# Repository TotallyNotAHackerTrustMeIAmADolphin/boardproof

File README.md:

# boardproof

An MCP server for PCB design in which nothing counts as finished unless a machine-checked gate says so. The Python package is `boardproof` and the start command is `boardproof`.

An MCP server that lets an AI agent do PCB design work in KiCad: component sourcing, schematic construction, placement, routing (KiCadRoutingTools or Freerouting), verification, SPICE simulation and manufacturing export. It drives KiCad through its files and `kicad-cli`, so no running KiCad is needed.

Who it is for: people who want an MCP client (Claude Code, Claude Desktop or another) to carry out real KiCad 10 work and who care more about a result they can trust than about a result that looks finished. Everything is built around one rule: a board is "done" only when a machine-checked verdict says so. A short tour of the design is in [docs/OVERVIEW.md](docs/OVERVIEW.md).

## Status (2026-10-29)

**No board has passed the acceptance gate as a plain PASS yet.** The tools exist and are tested, but no tool chain has delivered a routed board end to end that the gate accepts without a qualifier. Rung 1 has boards with `PASS (necked)` (protocol 6, Freerouting 5 of 5); the rung-1 board changed afterwards (protocols 7 and 8) and has no official batch under the current protocol. The product promise is therefore tiered by board class:

- **Copilot tier (default):** you own power routing and zone topology in KiCad. The agent handles schematic, placement, signal routing and verification.
- **Autonomous tier:** offered only for board classes that have passed the gate on the acceptance ladder. **Currently none.**

Words used below: a **rung** is one reference board on the acceptance ladder (an ordered set of boards a pipeline must pass, easiest first); **KRT** is KiCadRoutingTools, a third-party router this project runs as a subprocess; the **owner** is the person who decides the scope and rules of this project; a **build ticket N** is an internal work item id and may not be resolvable in a public copy (the fact is always stated in words next to it); a **protocol** is the frozen, numbered plan by which a rung is measured. [docs/CONTEXT.md](docs/CONTEXT.md) has the full glossary.

What the measurements say (five attempts per backend and rung, official batches, 2026-10-28):

| Rung | Board | Protocol | Freerouting 2.5.0 | KiCadRoutingTools 0.23.1 |
|---|---|---|---|---|
| 1 | USB-C ATtiny1616 breakout, 2 layers | 6 | 5 of 5 attempts `PASS (necked)` | 0 of 5 |
| 2 | KiCad's `pic_programmer` demo, tracks removed | 5 (no protocol-6 batch has run) | 0 of 5; cannot pass | 0 of 5; cannot pass |

- **`PASS (necked)`** means the board passed the gate (zero unconnected items, zero error-level DRC violations, all zones filled), but it carries counted necks: tracks narrower than their net class right at a pad entry, which the protocol accepts as "forced" when the pad geometry limits the width (at the 0.2 mm gap between U1's pads, a 0.2 mm track is the widest that keeps the class clearance). The Freerouting boards carry 3 such necks on `+3V3` at U1 pad 4, 2.1476 mm in total. It is a weaker statement than a plain PASS, it is always labelled, and no rung is claimed from it.
- **The 5 of 5 depends on one open decision.** The first segment of each neck is 0.15 mm wide where the pad would allow 0.2 mm. Under the protocol's current reading that still counts as forced; under a stricter reading all five attempts would FAIL. The owner's decision on a neck below the pad limit is still open (build ticket 111, item 3).
- KiCadRoutingTools scored 0 of 5 on rung 1 under protocol 6 because version 0.23.1 read the board's 10 unquoted pad names of the USB-C footprint as zero pads. The board and the router checkout have since changed (the checkout is pinned to a newer commit) and no official batch has run on them yet (build ticket 112 holds the guard).
- Rung 2 cannot pass for any router: the demo's own silkscreen already carries 6 `silk_overlap` errors, which no router can fix (build ticket 106).
- Rung 3, the 20 A class openMPPT board, is frozen until rungs 1 and 2 pass.

Details and the exact meaning of each number: [docs/ROADMAP.md](docs/ROADMAP.md) and [docs/TESTING.md](docs/TESTING.md).

## Quickstart

1. Install (below) and add the server to your MCP client (below).
2. Ask the agent to open a project: `project_open` takes a project directory or a `.kicad_pro` file. `project_create` scaffolds a new one.
3. Load what you need: `list_toolsets` shows the toolsets, `load_toolset` loads one (`schematic`, `placement`, `routing`, ...).
4. Grade the board: `pin_rule_baseline` before you start work, then `verify_board` with the board path, `parity="required"` (or `"not_applicable"` with a reason) and the baseline. Only a `PASS` from `verify_board` may be called routed or done.

## Install

Requirements:

- Python 3.11 or newer.
- KiCad 10 with `kicad-cli` (required). Tested with 10.0.7.
- Tested on Windows only (Windows 11, KiCad 10.0.7): every measurement and every gate run was made there. The code does not knowingly depend on Windows, but nothing has been run on Linux or macOS. Where docs/TESTING.md names Ubuntu paths, they are KiCad's package layout, not something this project has run.

Clone with submodules, so the JLCPCB library comes along (about 103 MB; it is optional, see below):

```
git clone --recurse-submodules <repository-url>
cd <the cloned folder>
```

Already cloned without them? `git submodule update --init --depth 1` fetches them afterwards.

```
python -m venv .venv
.venv/Scripts/pip install -e ".[dev,krt]"
```

easyeda2kicad (AGPL-3.0) is a core dependency, installed with the package and used as a subprocess only, never imported. Extras: `dev` (pytest, ruff), `krt` (the runtime dependencies of KiCadRoutingTools: numpy, scipy, shapely, Pillow), `copilot` (kicad-python, for the live-IPC adapter).

### External tools

Each tool is found the same way: an environment variable first, then `PATH`, then the usual install locations. A missing tool makes the tools that need it return `status: incomplete` with install instructions, never a guess.

| Tool | Used for | Environment variable |
|---|---|---|
| KiCad 10 `kicad-cli` | **Required.** DRC, ERC, netlists, renders, exports, the gate | `KICAD_CLI_PATH` |
| KiCad's bundled Python | Freerouting's Specctra export and import; KiKit | `KICAD_PYTHON_PATH` |
| KiCadRoutingTools v0.23.8, commit `c64c0db2` (MIT) | Routing and placement optimisation, run from a checkout. `python scripts/setup_krt.py` restores it into `.tools/KiCadRoutingTools` (the default; the variable wins) and fetches its prebuilt router, verified by SHA-256 | `KICAD_ROUTING_TOOLS_PATH`, `KICAD_ROUTING_TOOLS_PYTHON` |
| Freerouting 2.5.0 jar (GPLv3) and Java 25 | Routing, as a subprocess | `FREEROUTING_JAR_PATH`, `JAVA_PATH` |
| ngspice 47 (pinned; `ngspice_con.exe` on Windows) | SPICE simulation. **Optional while the simulation map is parked** (owner decision of 2026-10-30, issue 40): the batch gate does not require it, and its live tests skip, counted, when it is absent | `NGSPICE_PATH` |
| KiKit | Panelisation | `KIKIT_PATH` |
| KiCad's demo projects | Inputs of the second rung and of the oracle tests | `KICAD_DEMOS_DIR` |
| KiCad's symbol libraries | Schematic building and tests | `KICAD_SYMBOL_DIR` |

All third-party tools, their licences and how they are used are listed in [THIRD_PARTY.md](THIRD_PARTY.md).

### Optional: the JLCPCB symbol and footprint library

Whether a part is a JLCPCB Basic, Preferred or Extended part is answered from a small index that ships with the repository, with no download. The ready-made symbols, footprints and 3D models behind that index (CDFER/JLCPCB-Kicad-Library, MIT, about 103 MB) are a git submodule that a plain `git clone` does not fetch. Fetch it when you want them:

```
git submodule update --init --depth 1 third_party/JLCPCB-Kicad-Library
```

Without it, asset lookups fall back to `easyeda2kicad` (a core dependency) and say so. The server looks for the library in this order: the `BOARDPROOF_JLCPCB_LIBRARY` environment variable, the submodule above, KiCad's third-party directory (a Plugin and Content Manager install). `jlcpcb_library_status` reports what it found and, for an empty or missing submodule, the command above. A new git worktree starts with the submodule empty; set `BOARDPROOF_JLCPCB_LIBRARY` to another checkout's `third_party/JLCPCB-Kicad-Library` to share it. To rebuild the index after moving the pin: `python scripts/refresh_jlcpcb_index.py`.

#### Refreshing the library to upstream's newest commit

The pin stays on one commit so the shipped index is reproducible. To move it, run in a checkout whose submodule is initialised (the command above), from a clean tree:

```
python scripts/refresh_jlcpcb_index.py --update --dry-run   # plan only: fetches into a scratch repository, changes nothing here
python scripts/refresh_jlcpcb_index.py --update             # moves the pin, rewrites the index, stages both
```

It prints upstream's commit, the part counts and every part that changes tier (Basic, Preferred, Extended), then stages the new submodule commit and the index; you review and commit. It refuses, and moves nothing, when a symbol library that holds parts today holds none upstream (`library_emptied`), when the part count falls below 80% of the old one (`index_would_shrink`) or when a symbol file fails to parse. There is no override flag: to follow a real loss, move the pin by hand. The apply is all-or-nothing: if the index replace, the submodule checkout or `git add` fails, the old submodule commit, the old index bytes and the old staging are put back (or the exact commands to do so are printed). `--ref` must be a plain ref name and `--upstream` an https URL (a local directory only when typed on the command line); every fetch runs with `--` and with all git transports except https (and a typed local path) switched off. Upstream's newest commit was still broken when this was written (18 of 20 symbol files hold only a header), so the command refuses it today. Without the submodule the dry run works and the real run says what to fetch first.

## MCP client configuration

```json
{
  "mcpServers": {
    "boardproof": {
      "command": "path/to/.venv/Scripts/python",
      "args": ["-m", "boardproof.server"]
    }
  }
}
```

The installed script does the same: `"command": "path/to/.venv/Scripts/boardproof"` with no arguments.

Renamed from kicad-mcp (package `kicad_mcp`, environment prefix `KICAD_MCP_`) in build ticket 74: the package, the start command and the MCP server name are `boardproof`, and the environment variables `KICAD_MCP_*` are now `BOARDPROOF_*` with no fallback. After pulling the rename run `pip install -e .` again in the virtual environment and change the MCP client configuration (`-m kicad_mcp.server` becomes `-m boardproof.server`). Schematic backups made before the rename stay in the old backup directory (`%LOCALAPPDATA%\kicad-mcp\schematic-backups`) and are not read by the new name.

The server starts with 19 tools: the three toolset tools (`list_toolsets`, `load_toolset`, `unload_toolset`), `project_create`, `project_open`, the gate (`verify_board`, `pin_rule_baseline`) and the checkpointed pairs for input preparation, pour step, schematic import, board rules, board outline and silkscreen minimums. Ten more toolsets load on demand with `load_toolset`: `verification` (9 tools), `sourcing` (13), `diagnostics` (2), `library` (3), `schematic` (7), `placement` (12), `manufacturing` (2), `routing` (6), `copilot` (9) and `simulation` (2). That is 65 more tools, 84 in total (counted from a running server on 2026-10-29).

## Usage log (local, anonymous, off with one variable)

The server keeps a small log of which of its own tools get called, so that unused tools can be found and slow ones fixed. It is **on by default and stays on your machine**: nothing is sent anywhere, and the logging code imports no networking module (a test checks it).

- **What is recorded**, one JSON line per tool call: the UTC start time, the tool's name, its toolset, the duration in milliseconds, the outcome (one of a fixed set of words: `ok`, `error`, `cancelled`, or the result's own status word such as `PASS`, `FAIL` or `INCOMPLETE` if it is on the reviewed list in `usage_log.RESULT_WORDS`; any other word is recorded as `other`, never copied) and a random id that is new for each server process.
- **What is never recorded:** arguments, results, file paths, part numbers, net names, user or machine names, environment values.
- **Where:** `usage.jsonl` in the `boardproof` folder of `%LOCALAPPDATA%` on Windows, `~/Library/Application Support/boardproof/usage.jsonl` on macOS, `$XDG_DATA_HOME/boardproof/usage.jsonl` (else `~/.local/share/boardproof/usage.jsonl`) elsewhere. The file is capped at 1 MB and rotates once to `usage.jsonl.1`. Set `BOARDPROOF_USAGE_LOG` to a file path to write there instead.
- **Turn it off:** set `BOARDPROOF_USAGE_LOG=off` in the server's environment (for example in the `env` block of the MCP client configuration). **Delete it:** delete `usage.jsonl` and `usage.jsonl.1`.
- **Read it:** `python scripts/usage_report.py` prints, per tool, the count, share, median and 95th-percentile duration, error rate and last use, then the tools that were never called (`--since DAYS`, `--json`, `--log FILE`).

## Principles

- **Evidence-gated:** a check that did not fully run says so and never reports clean.
- **`kicad-cli` is the judge:** structured DRC and ERC output, read in full. Renders are for humans only.
- **Batch tools:** operations take collections, not one item per call.
- **Checkpoints:** autorouting, autoplacement, ambiguous part matches and destructive edits return a proposal and a revision token. Nothing is written until you confirm, and for the newer checkpoint pairs a confirm is refused if the project's files changed in between.
- **Never hand-edit KiCad files:** every mutation goes through this project's tools, or through the project's write layer (`boardproof.write_layer`), which saves through a temporary file, a parse check and `os.replace`.

## Limitations

- **Sourcing:** Nexar and Digi-Key providers are not built (they need credentials). The LCSC provider is blocked by a bot wall and returns an error rather than an empty list. The JLCPCB Basic parts index is vendored.
- **Autoplacement** (`propose_autoplacement`) is a naive row-packer. KiCadRoutingTools' placement optimiser is the stronger option.
- **Zones:** there is a pour step (`propose_pour_step` and `confirm_pour_step`) that adds a gate-graded plane zone from KiCadRoutingTools' plane script. There is no general zone-editing tool and no track or via removal tool.
- **Schematic editing tools** are unsafe on hierarchical (multi-sheet) projects; see [docs/ARCHITECTURE.md](docs/ARCHITECTURE.md), "Known facts and gotchas".
- **Windows only** so far.

## Tests

Several thousand tests (the current count is the last line of `python -m pytest --collect-only -q -m "not network"`). From the repository root:

```
python -m pytest -m "not network"
```

Tests that need an external tool skip with a stated reason when the tool is absent. The full gate, `python scripts/batch_gate.py`, runs the whole suite and the linter in a clean tree and ends with one `GREEN` or `RED` line; it takes about 45 minutes. There is no hosted CI: that local gate is the test gate. See [docs/TESTING.md](docs/TESTING.md).

## Documentation

| File | Contents |
|---|---|
| [docs/OVERVIEW.md](docs/OVERVIEW.md) | A ten-minute tour: how a tool call works, the gate, the ladder |
| [docs/CONTEXT.md](docs/CONTEXT.md) | Glossary |
| [docs/ARCHITECTURE.md](docs/ARCHITECTURE.md) | The decision record and the known facts and gotchas, with evidence |
| [docs/ROADMAP.md](docs/ROADMAP.md) | The acceptance ladder, carried-over defects, non-goals |
| [docs/TESTING.md](docs/TESTING.md) | The acceptance gate and the test suite |
| [CONTRIBUTING.md](CONTRIBUTING.md) | How to contribute |
| [THIRD_PARTY.md](THIRD_PARTY.md) | Third-party tools and data, with licences |
| [CLAUDE.md](CLAUDE.md) | Rules for AI agents working in this repository |

## Contributing and licence

Contributions are welcome; read [CONTRIBUTING.md](CONTRIBUTING.md) first. The code is MIT-licensed ([LICENSE](LICENSE)). Copyleft tools (Freerouting, easyeda2kicad) are only ever run as subprocesses. `kiutils` (GPLv3) is not used.

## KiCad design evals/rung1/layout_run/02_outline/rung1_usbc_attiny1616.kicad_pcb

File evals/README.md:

# Evaluation suite

`boardproof_eval.xml` holds 15 independent, read-only Q&A pairs. Each tests whether an agent with only this project's tools can answer a realistic question about the fixtures in `tests/fixtures/`. The format follows the `mcp-builder` evaluation guide. The suite tests tool usability, not board quality; the acceptance gate (docs/TESTING.md) handles that.

- **Q1-Q10:** single-tool lookups (DRC/ERC on `simple_led`, footprint counts, symbol values, the parametric footprint generator, datasheet extraction).
- **Q11-Q15:** multi-step chains:
  - Q11: collision check, then placement check.
  - Q12: DRC, then the unrouted-net query ("0 violations" does not mean fab-ready).
  - Q13: ERC, then SPICE export, then reading the netlist.
  - Q14: datasheet, then footprint generation, then minimal KLC.
  - Q15: open the project, run the manufacturing export, read the BOM and CPL.

## Rules for answers

- Every answer must be derived by **running the tool against the real fixture**, never by reasoning it out.
- **Pin answers to facts the fixture file determines,** not to facts the toolchain determines. `lib_footprint_mismatch` counts follow whichever KiCad stock libraries are installed, and they have already drifted once (1 became 3). Values set by `kicad_tools` internals are stated as properties ("at least 7 package types") and not as exact values.
- **No question depends on a live sourcing provider.**
- **No question mutates a fixture.** Exports go to temporary directories.

## Running

Use the `mcp-builder` evaluation script (`~/.claude/skills/mcp-builder/scripts/evaluation.py`) against this server. Or run it by hand: give an agent the tools and the questions, then diff its answers against the `<answer>` values.

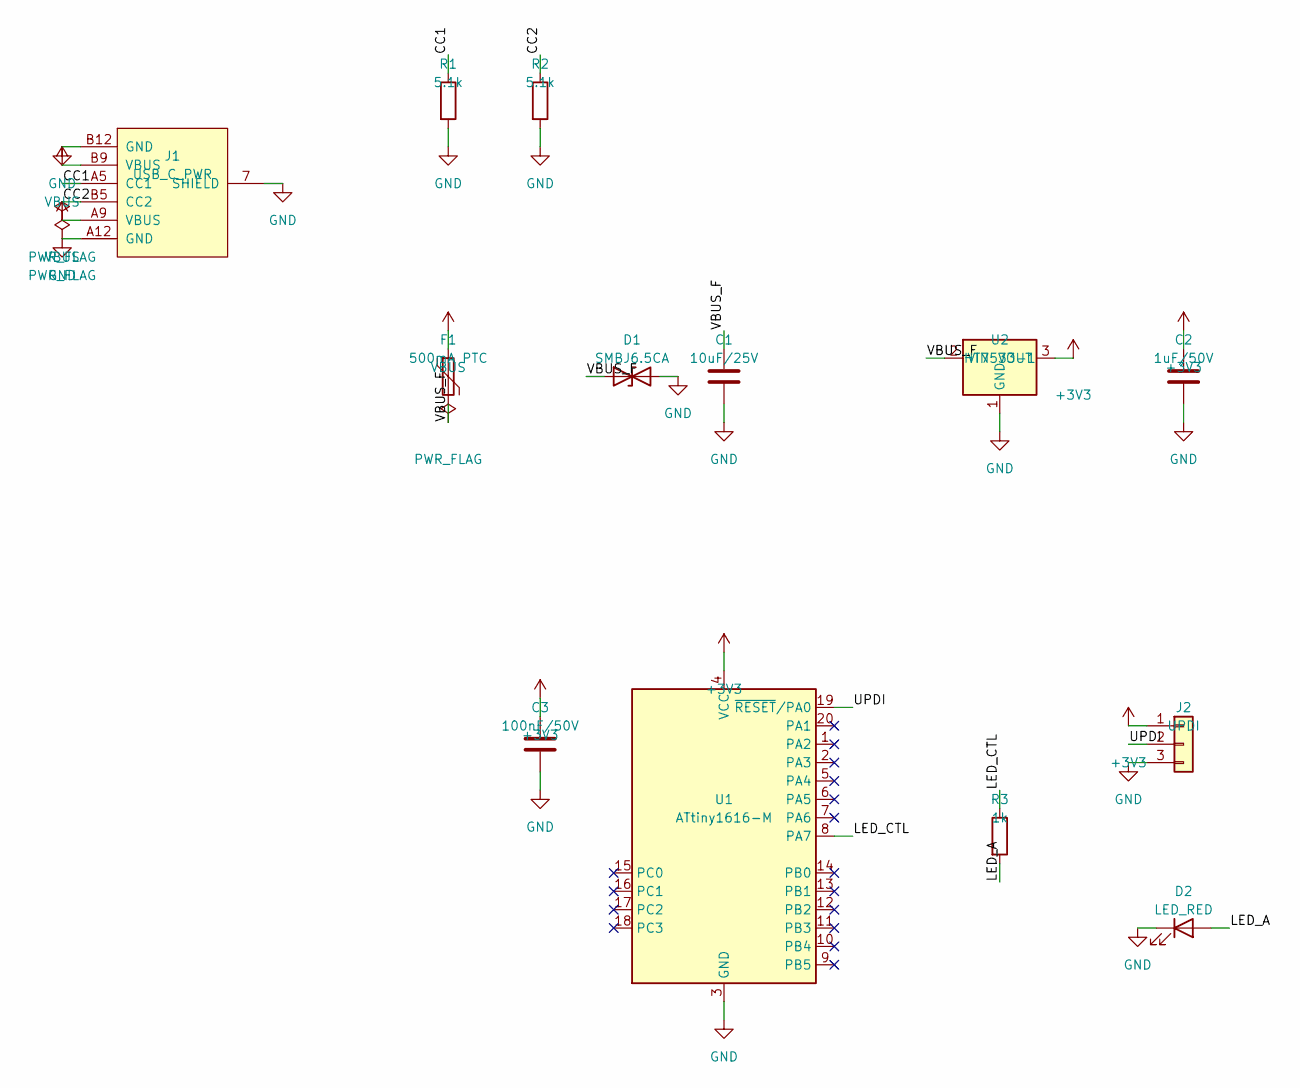
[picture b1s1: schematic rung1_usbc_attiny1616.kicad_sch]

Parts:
C1: 10uF/25V; C_0805_2012Metric; MPN CL21A106KAYNNNE; LCSC C15850
C2: 1uF/50V; C_0603_1608Metric; MPN CL10A105KB8NNNC; LCSC C15849
C3: 100nF/50V; C_0603_1608Metric; MPN CC0603KRX7R9BB104; LCSC C14663
D1: SMBJ6.5CA; D_SMB; MPN SMBJ6.5CA; LCSC C7420377
D2: LED_RED; LED_0603_1608Metric; MPN KT-0603R; LCSC C2286
F1: 500mA PTC; Fuse_0805_2012Metric; MPN SMD0805P050TF; LCSC C20978
J1: USB_C_PWR; USB_C_Receptacle_Shouhan_TYPE-C-6P; MPN TYPE-C 6P (SHOU HAN); LCSC C456012
J2: UPDI; PinHeader_1x03_P2.54mm_Vertical; MPN 2.54-1*3PIN (BOOMELE); LCSC C49257
R1, R2: 5.1k; R_0603_1608Metric; MPN 0603WAF5101T5E; LCSC C23186
R3: 1k; R_0603_1608Metric; MPN 0603WAF1001T5E; LCSC C21190
U1: ATtiny1616-M; VQFN-20-1EP_3x3mm_P0.4mm_EP1.7x1.7mm; MPN ATTINY1616-MNR; LCSC C507118
U2: HT7533-1; SOT-89-3; MPN HT7533-1; LCSC C14289

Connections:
+3V3: C2.1, C3.1, J2.1, U1.4 (VCC), U2.3 (VOUT)
/CC1: J1.A5 (CC1), R1.1
/CC2: J1.B5 (CC2), R2.1
/LED_A: D2.2 (A), R3.2
/LED_CTL: R3.1, U1.8 (PA7)
/UPDI: J2.2, U1.19 (~RESET/PA0)
/VBUS_F: C1.1, D1.1 (A1), F1.2, U2.2 (VIN)
GND: C1.2, C2.2, C3.2, D1.2 (A2), D2.1 (K), J1.7 (SHIELD), J1.A12 (GND), J1.B12 (GND), J2.3, R1.2, R2.2, U1.3 (GND), U1.21 (GND), U2.1 (GND)
VBUS: F1.1, J1.A9 (VBUS), J1.B9 (VBUS)

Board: 2 copper layers, 17 parts (0 on the bottom side), 9 nets, no tracks yet.

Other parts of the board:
H1, H2, H3, H4: MountingHole_2.2mm_M2

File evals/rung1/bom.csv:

Designator,Comment,Footprint,LCSC Part #,MPN,Tier
C1,10uF/25V,Capacitor_SMD:C_0805_2012Metric,C15850,CL21A106KAYNNNE,basic
C2,1uF/50V,Capacitor_SMD:C_0603_1608Metric,C15849,CL10A105KB8NNNC,basic
C3,100nF/50V,Capacitor_SMD:C_0603_1608Metric,C14663,CC0603KRX7R9BB104,basic
D1,SMBJ6.5CA,Diode_SMD:D_SMB,C7420377,SMBJ6.5CA,basic
D2,LED_RED,LED_SMD:LED_0603_1608Metric,C2286,KT-0603R,basic
F1,500mA PTC,Fuse:Fuse_0805_2012Metric,C20978,SMD0805P050TF,extended
J1,USB_C_PWR,Rung1_USBC:USB_C_Receptacle_Shouhan_TYPE-C-6P,C456012,TYPE-C 6P (SHOU HAN),extended
J2,UPDI,Connector_PinHeader_2.54mm:PinHeader_1x03_P2.54mm_Vertical,C49257,2.54-1*3PIN (BOOMELE),extended
R1,5.1k,Resistor_SMD:R_0603_1608Metric,C23186,0603WAF5101T5E,basic
R2,5.1k,Resistor_SMD:R_0603_1608Metric,C23186,0603WAF5101T5E,basic
R3,1k,Resistor_SMD:R_0603_1608Metric,C21190,0603WAF1001T5E,basic
U1,ATtiny1616-M,Package_DFN_QFN:VQFN-20-1EP_3x3mm_P0.4mm_EP1.7x1.7mm,C507118,ATTINY1616-MNR,extended
U2,HT7533-1,Package_TO_SOT_SMD:SOT-89-3,C14289,HT7533-1,basic

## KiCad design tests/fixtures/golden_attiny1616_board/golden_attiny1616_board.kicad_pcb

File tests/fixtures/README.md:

# Test fixtures

Every purpose-built fixture is generated through `kicad_tools`' own object model (`PCB.create`, footprints, nets, `SExp`) and saved through the write layer (`write_layer.save_pcb`, which parse-checks it with `kicad-cli`; build ticket 42), or filled by `kicad-cli`. None is hand-typed (CLAUDE.md rule 1).

| Fixture | Origin | Purpose |
|---|---|---|
| `simple_led.*` | Copied from rjwalters/kicad-tools `00-simple-led` (MIT) | Small, valid real KiCad files for `kicad-cli` and `kicad_tools` calls. KiCad 7-style refs, which is why it missed the KiCad 8+ DSN reference bug. |
| `golden_attiny1616_board/` | Built by the pipeline (v1, 2026-09-02) | Pipeline regression fixture. **Unrouted. It has a generic power header instead of USB-C, and its 0.2/0.2 rules cannot be routed at the VQFN's 0.4 mm pitch.** Not a rung-1 candidate (TESTING.md). |
| `graphics_removal_board.kicad_pcb` | Purpose-built | `propose_remove_graphic_items` tests: six graphics across `gr_rect`, `gr_poly`, `gr_line`, `gr_circle` and `gr_arc`, net-tagged copper plus silkscreen. |
| `zone_obstacle/` | `simple_led` plus a real GND pour filled by `kicad-cli --refill-zones` | Reproduces "filled zone is not an obstacle for a foreign net": KRT routes LED_ANODE at 0.0 mm clearance to the GND zone. |
| `krt_stress_congestion.*` | Purpose-built, 30x36 mm, 2-layer, with a real sibling `.kicad_pro` | KRT placement and blocking-analysis tests. An LQFP-48 with 5 signal nets crosses an 8-pin THT header wall, modelled on openMPPT's GPIO1 bottleneck. KRT routes 4 of 5 nets in about 4 s. `SIG5` fails as `boxed_in_static`, but `check_reachability.py` says the net is PASSABLE, so this is a search miss, not real congestion. |
| `krt_pad_geometry_isolated.*` | Purpose-built | Isolates whether pad size alone blocks a route. With 2.2 mm header pads (0.34 mm gap), `SIG1` fails after more than 227k A\* iterations. Shrunk to the JLCPCB floor of 1.36 mm (1.0 drill + 2 x 0.18 annular), it routes as one direct trace. The shrink must mutate the `(size)` node, because `pad.size = ...` is not saved. |
| `openmppt_v1_3.kicad_dru` | Copied from the user's openMPPT board | A real custom-rules file for `board_rules` matching (`hole_to_hole` vs `hole_clearance`). |
| `datasheets/` | TI LM358, onsemi NCV7691, Nexperia PMEG2005EJ | `inspect_datasheet` tests. |
| `uw/r2krt`, `uw/r1krt`, `uw/r1fr` | Taken byte-for-byte from the committed run directories of `paradigm-review-2` ticket 04 (2026-10-19, KRT rung 2, KRT rung 1, Freerouting rung 1): `in/` holds the batch's frozen `.kicad_pcb` and `.kicad_pro`, `out/` the board attempt 00 delivered; `attempt0.json` holds that attempt's recorded router facts with machine paths replaced by `<path>` (by `scripts/export_ladder_results.py`' sanitiser) | `tests/test_krt_under_width_delivery.py`, `tests/test_rung_backends_under_width.py`: the under-width replays. These were read from `.scratch` before the run directories left the repository. |

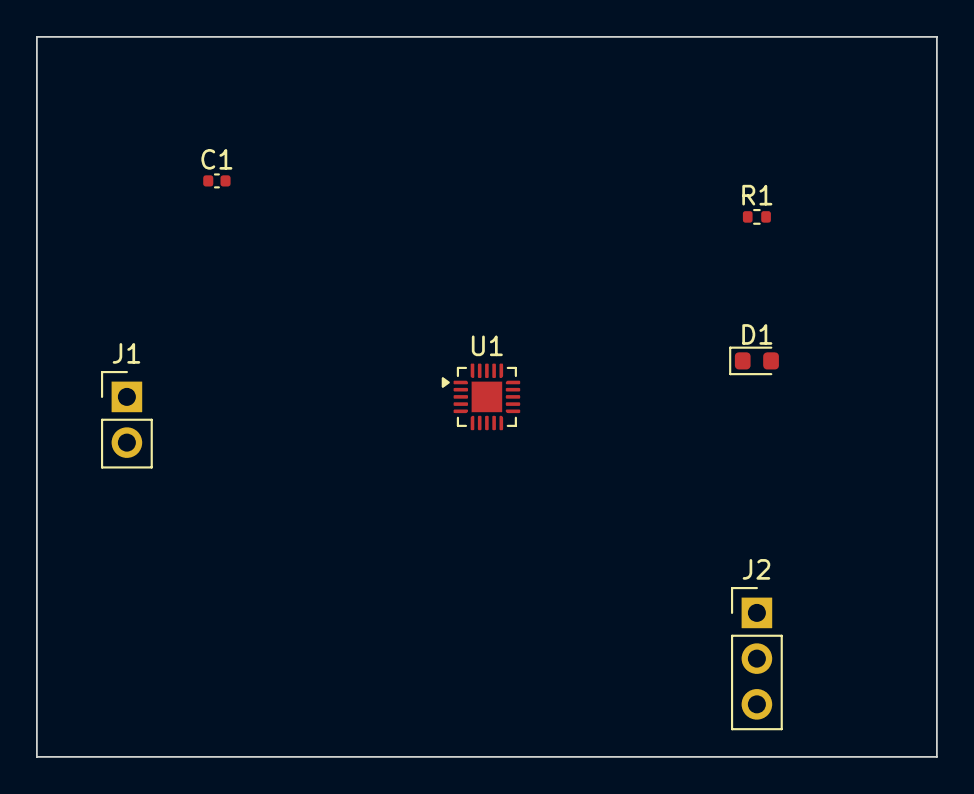
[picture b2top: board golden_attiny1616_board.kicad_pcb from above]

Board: 2 copper layers, 50.0 x 40.0 mm, 6 parts (0 on the bottom side), 5 nets, no tracks yet.

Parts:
C1: 100nF; C_0402_1005Metric
D1: LED; LED_0603_1608Metric
J1: PWR_IN; PinHeader_1x02_P2.54mm_Vertical
J2: UPDI; PinHeader_1x03_P2.54mm_Vertical
R1: 1k; R_0402_1005Metric
U1: ATtiny1616-M; VQFN-20-1EP_3x3mm_P0.4mm_EP1.7x1.7mm

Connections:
GND: C1.2, D1.2, J1.2, J2.3, U1.3, U1.21
unnamed: D1.1, R1.2
unnamed: J2.2, U1.19
unnamed: R1.1, U1.20
VCC: C1.1, J1.1, J2.1, U1.4

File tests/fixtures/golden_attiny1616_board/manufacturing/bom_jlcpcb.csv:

Comment,Designator,Footprint,LCSC Part #
100nF,C1,Capacitor_SMD:C_0402_1005Metric,
1k,R1,Resistor_SMD:R_0402_1005Metric,
ATtiny1616-M,U1,Package_DFN_QFN:VQFN-20-1EP_3x3mm_P0.4mm_EP1.7x1.7mm,
LED,D1,LED_SMD:LED_0603_1608Metric,
PWR_IN,J1,Connector_PinHeader_2.54mm:PinHeader_1x02_P2.54mm_Vertical,
UPDI,J2,Connector_PinHeader_2.54mm:PinHeader_1x03_P2.54mm_Vertical,

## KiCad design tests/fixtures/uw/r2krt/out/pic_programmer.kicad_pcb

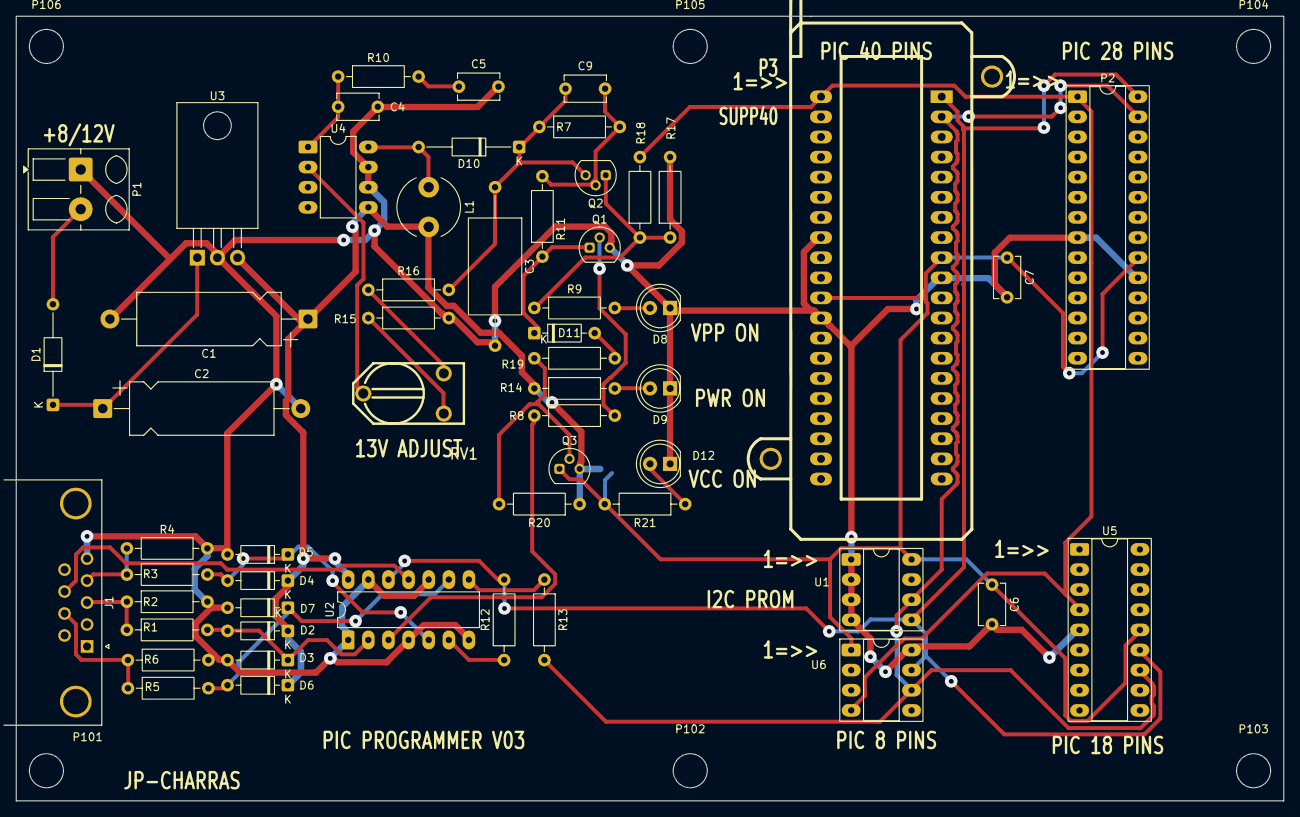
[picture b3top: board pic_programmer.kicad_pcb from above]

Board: 2 copper layers, 160.0 x 99.1 mm, 63 parts (1 on the bottom side), 34 nets.

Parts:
C1: 100µF; CP_Axial_L18.0mm_D6.5mm_P25.00mm_Horizontal
C2: 220uF; CP_Axial_L18.0mm_D6.5mm_P25.00mm_Horizontal
C3: 22uF/25V; C_Axial_L12.0mm_D6.5mm_P20.00mm_Horizontal
C4: 0; C_Disc_D5.1mm_W3.2mm_P5.00mm
C5: 10nF; C_Disc_D5.1mm_W3.2mm_P5.00mm
C6, C7: 100nF; C_Disc_D5.1mm_W3.2mm_P5.00mm
C9: 220nF; C_Disc_D5.1mm_W3.2mm_P5.00mm
D1: 1N4004; D_DO-35_SOD27_P12.70mm_Horizontal
D2, D3, D4, D5, D6, D7, D11: BAT43; D_DO-35_SOD27_P7.62mm_Horizontal
D8: RED-LED; LED_D5.0mm
D9: GREEN-LED; LED_D5.0mm
D10: SCHOTTKY; D_DO-35_SOD27_P12.70mm_Horizontal
D12: YELLOW-LED; LED_D5.0mm
J1: DB9-FEMAL; DSUB-9_Socket_Horizontal_P2.77x2.84mm_EdgePinOffset7.70mm_H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
JP1: JUMPER; SolderJumper-2_P1.3mm_Open_TrianglePad1.0x1.5mm
L1: 22uH; L_Radial_D7.8mm_P5.00mm_Fastron_07HCP
P1: CONN_2; Altech_AK300_1x02_P5.00mm_45-Degree
P2: SUPP28; DIP-28_W7.62mm_Socket_LongPads
P3: SUPP40; 40tex-Ell600
P101, P102, P103, P104, P105, P106: CONN_1; MountingHole_4.3mm_M4
Q1: BC237; TO-92
Q2, Q3: BC307; TO-92
R1, R2, R3, R4, R5, R6, R7: 10K; R_Axial_DIN0207_L6.3mm_D2.5mm_P10.16mm_Horizontal
R8: 1K; R_Axial_DIN0207_L6.3mm_D2.5mm_P10.16mm_Horizontal
R9, R19, R20: 2.2K; R_Axial_DIN0207_L6.3mm_D2.5mm_P10.16mm_Horizontal
R10: 5,1K; R_Axial_DIN0207_L6.3mm_D2.5mm_P10.16mm_Horizontal
R11, R17: 22K; R_Axial_DIN0207_L6.3mm_D2.5mm_P10.16mm_Horizontal
R12, R13, R14, R21: 470; R_Axial_DIN0207_L6.3mm_D2.5mm_P10.16mm_Horizontal
R15: 6.2K; R_Axial_DIN0207_L6.3mm_D2.5mm_P10.16mm_Horizontal
R16: 62K; R_Axial_DIN0207_L6.3mm_D2.5mm_P10.16mm_Horizontal
R18: 220; R_Axial_DIN0207_L6.3mm_D2.5mm_P10.16mm_Horizontal
RV1: 1K; RV2X4
U1: 24Cxx; DIP-8_W7.62mm_Socket_LongPads
U2: 74HC125; DIP-14_W7.62mm_LongPads
U3: 7805; TO-220-3_Horizontal_TabDown
U4: LT1373; DIP-8_W7.62mm_LongPads
U5: PIC_18_PINS; DIP-18_W7.62mm_Socket_LongPads
U6: PIC_8_PINS; DIP-8_W7.62mm_Socket_LongPads

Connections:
/CLOCK-RB6: P2.27, P3.39, R13.2, U1.6 (SCL), U5.12 (ICSPC/RB6), U6.6 (GP1)
/DATA-RB7: P2.28, P3.40, R12.2, U1.5 (SDA), U2.12, U5.13 (ICSPD/RB7), U6.7 (GP0)
/PC-CLOCK-OUT: J1.7, R5.1, R6.1
/PC-DATA-IN: J1.8, U2.11
/PC-DATA-OUT: J1.4, R3.1, R4.1
/VPP_ON: J1.3, R1.1, R2.1
/VPP/MCLR: P2.1, P3.1, R18.2, U5.4 (MCLR), U6.4 (GP3/MCLR)
/pic_sockets/VCC_PIC: C6.1, C7.1, JP1.2, P2.20, P3.11, P3.32, Q3.1 (C), R21.2, U1.8 (VCC), U5.14 (VDD), U6.1 (VDD)
GND: C1.2, C2.2, C3.2, C4.2, C5.2, C6.2, C7.2, D3.2 (A), D5.2 (A), D7.2 (A), D8.1 (K), D9.1 (K), D12.1 (K), J1.5, P1.1, P2.8, P2.19, P3.8, P3.12, P3.31, Q1.3 (E), R2.2, R4.2, R6.2, R15.2, R17.2, U1.1 (A0), U1.2 (A1), U1.3 (A2), U1.4 (GND), U2.1, U2.4, U2.7 (GND), U2.10, U2.13, U3.2 (GND), U4.6 (GND_S), U4.7 (GND), U5.5 (VSS), U6.8 (VSS)
unnamed: C5.1, R10.2
unnamed: D1.2 (A), P1.2 (PM)
unnamed: C2.1, D1.1 (K), U3.1 (VI)
unnamed: D2.2 (A), D3.1 (K), R1.2, U2.2
unnamed: D4.2 (A), D5.1 (K), R3.2, U2.5
unnamed: D6.2 (A), D7.1 (K), R5.2, U2.9
unnamed: D8.2 (A), R9.2
unnamed: D9.2 (A), R14.2
unnamed: D10.2 (A), L1.1, U4.8 (Vsw)
unnamed: D11.2 (A), R19.1
unnamed: D11.1 (K), Q1.1 (C), R11.1
unnamed: D12.2 (A), R21.1
unnamed: Q1.2 (B), R8.2
unnamed: C9.2, Q2.2 (B), R7.2, R11.2
unnamed: Q2.1 (C), R9.1, R17.1, R18.1
unnamed: Q3.2 (B), R19.2, R20.2
unnamed: R8.1, U2.3
unnamed: R12.1, U2.6
unnamed: R13.1, U2.8
unnamed: R15.1, RV1.1
unnamed: R16.1, RV1.3
unnamed: RV1.2, U4.2 (FB+)
unnamed: C4.1, R10.1, U4.1 (Vc)
VCC: C1.1, D2.1 (K), D4.1 (K), D6.1 (K), JP1.1, L1.2, Q3.3 (E), R14.1, R20.1, U2.14 (VCC), U3.3 (VO), U4.5 (Vin)
VPP: C3.1, C9.1, D10.1 (K), Q2.3 (E), R7.1, R16.2

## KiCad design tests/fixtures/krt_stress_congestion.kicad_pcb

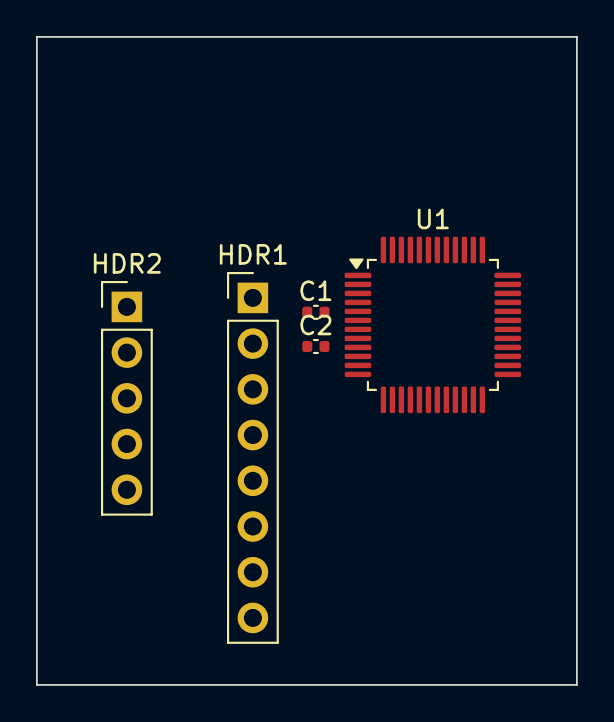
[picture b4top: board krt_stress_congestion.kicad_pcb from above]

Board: 2 copper layers, 30.0 x 36.0 mm, 5 parts (0 on the bottom side), 7 nets, no tracks yet.

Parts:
C1, C2: C_0402_1005Metric
HDR1: PinHeader_1x08_P2.54mm_Vertical
HDR2: PinHeader_1x05_P2.54mm_Vertical
U1: LQFP-48_7x7mm_P0.5mm

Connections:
GND: C1.2, C2.2, HDR1.2, HDR1.4, HDR1.6, HDR1.8
SIG1: HDR2.1, U1.5
SIG2: HDR2.2, U1.6
SIG3: HDR2.3, U1.7
SIG4: HDR2.4, U1.8
SIG5: HDR2.5, U1.9
VDD: C1.1, C2.1, HDR1.1, HDR1.3, HDR1.5, HDR1.7

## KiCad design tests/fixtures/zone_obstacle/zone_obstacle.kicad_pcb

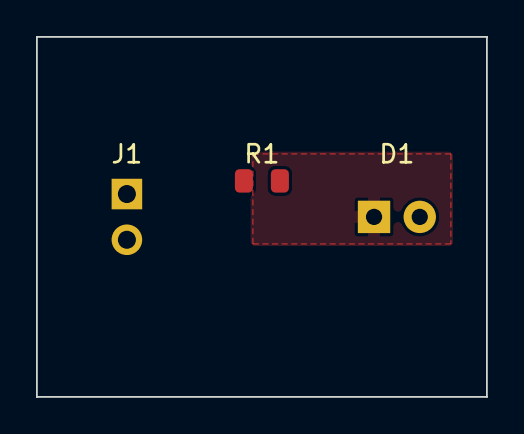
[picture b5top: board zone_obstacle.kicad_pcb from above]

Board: 2 copper layers, 25.0 x 20.0 mm, 3 parts (0 on the bottom side), 3 nets, no tracks yet.

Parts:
D1: LED; LED_D5.0mm
J1: PWR; PinHeader_1x02_P2.54mm_Vertical
R1: 330; R_0805_2012Metric

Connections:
GND: D1.1, J1.2
LED_ANODE: D1.2, R1.2
VCC: J1.1, R1.1

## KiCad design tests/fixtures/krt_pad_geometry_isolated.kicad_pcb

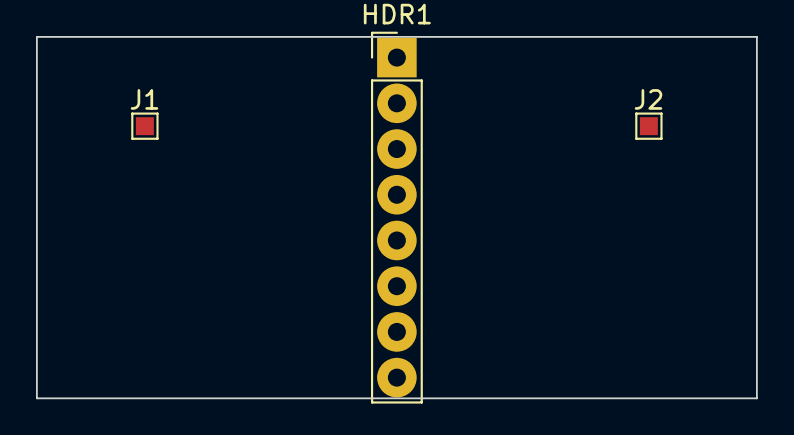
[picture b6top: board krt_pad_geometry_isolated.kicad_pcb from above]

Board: 2 copper layers, 40.0 x 20.1 mm, 3 parts (0 on the bottom side), 2 nets, no tracks yet.

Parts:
HDR1: PinHeader_1x08_P2.54mm_Vertical
J1, J2: TestPoint_Pad_1.0x1.0mm

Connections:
GND: HDR1.1, HDR1.2, HDR1.3, HDR1.4, HDR1.5, HDR1.6, HDR1.7, HDR1.8
SIG1: J1.1, J2.1
